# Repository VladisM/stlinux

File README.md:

# STlinux

Simple board with STM32F446 and SDRAM that is capable of running MMU less linux
build. Purpose of this project is to learn new stuffs. It may seems like good
thing to have Linux in such small form factor but it isn't. MMU is somehow
important in security and using this approach to build device that will be
connected to the network is a bad idea.

This project using submodules. After clone use following to init them.

```bash
$ git submodule update --init --recursive
```

## System specification

* Hardware:
    * 32MB SDRAM
    * 8MB QSPI Flash
    * UART console, sd card slot, EEPROM
    * two LEDs and two buttons
* Software
    * Linux kernel 6.3
    * Busybox 1.36.1

## Manufacturing board

Gerber files required for manufacturing are stored in `board/ger` subdirectory.
To manufacture board you shall just find yourself a suitable manufacturer
and use latest archive.

To generate BOM you shall use KiCad and revisit folder `board/kicad`. All
project files are stored there.

After soldering board you should apply ftdi configuration into
integrated UART bridge. Correct configuration is provided
by the file `board/ftdi_configuration.xml`. For that you are going
to need Windows PC and FT_PROG tool (available on their website).

To test if board was correctly manufactured and most importantly
assembled. You can use firmware available in `board_test` folder.

Compile and load firmware, connect using serial port at speed of 115200
and follow instructions.

**Warning:** at this moment SDIO and SD Card slot test are
not implemented!

## Compile system and bootloader

Everything is compiled using clfs.sh script in root folder of this project. So,
if you want to compile whole system simply call following command. (note, adjust
number of cores for compilation using -j)

```bash
$ ./clfs.sh --build all -j 8
```

After some time, you can find all output images in `build/images/`. There are:

 * bootloader - u-boot.bin
 * linux kernel - zImage
 * device tree - stm32f446-stlinux.dtb
 * system image - clfs.uImage

Bootloader shall be loaded to the board using STLink, and shall be written
to the internal Flash memory of MCU.

```bash
st-flash write build/images/u-boot.bin 0x08000000
```

Other components are by default loaded from QSPI Flash, there are two ways how
to get them there.

 * Using SD card
 * Using serial port (legacy)

### Loading QSPI Flash using serial port

This method was used for first revision of board with nonworking SD card slot.
If you have second revision of board, use SD card, it is much more faster.

Once you are in u-boot console, you can use xmodem protocol to send all files
and then write them to the QSPI Flash. For writing there is mtd command. Follow
next code snippet.

```bash
> loadx
# send kernel file (zImage) using your console emulator
> mtd erase kernel
> mtd write kernel ${loadaddr}
> loadx
# send rootfs file (clfs.uImage) using your console emulator
> mtd erase rootfs
> mtd write rootfs ${loadaddr}
> loadx
# send dtb file (stm32f446-stlinux.dtb) using your console emulator
> mtd erase rootfs
> mtd write rootfs ${loadaddr}
```

Then you can simply reset the board or type `run bootcmd` and you should be
welcomed by kernel boot log.

### Loading QSPI Flash using SD card

Compared to using serial port, this one is much much faster because data are
transferred over SD card, not xmodem at 115200 bauds.

Create one partition on your SD card, format it as FAT32, and copy there
image files from build directory. Then insert your card to the board and run
following commands.

```bash
> fatload mmc 0:1 ${loadaddr} zImage
> mtd erase kernel
> mtd write kernel ${loadaddr}
> fatload mmc 0:1 ${loadaddr} clfs.uImage
> mtd erase rootfs
> mtd write rootfs ${loadaddr}
> fatload mmc 0:1 ${loadaddr} stm32f446-stlinux.dtb
> mtd erase dtb
> mtd write dtb ${loadaddr}
```

After reset, your board will boot from QSPI Flash or you can simply type
`run bootcmd`.

### Loading directly from SD card

If you are feeling lazy, just copypaste this to bootloader console. And it will boot.

```bash
fatload mmc 0:1 ${kernel_addr_l} zImage ; fatload mmc 0:1 ${rootfs_addr_l} clfs.uImage ; fatload mmc 0:1 ${dtb_addr_l} stm32f446-stlinux.dtb ; run set_args ; bootz ${kernel_addr_l} ${rootfs_addr_l} ${dtb_addr_l}
```

It will load everything from SD card into RAM and boot kernel that way.

## License

This project is using a lot of software components that are licensed under
various licenses. Always make sure to check what component are you working
with to prevent any misunderstanding.

Board manufacturing files, firmware for testing, and build script is licensed
using the Do What The Fuck You Want To Public License, Version 2,
as published by Sam Hocevar. See COPYING file for more details.

Note: CLFS is abbreviation from Cross Linux From Scratch, in general describing process
of cross compiling [Linux From Scratch](https://www.linuxfromscratch.org/). Please
also see [CLFS project](https://trac.clfs.org/). My work is influenced by these
projects and I learned from their materials a lot.

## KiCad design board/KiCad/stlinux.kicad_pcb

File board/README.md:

# Board project files

In this directory all files required for manufacturing board are gathered.
Archives with gerber files are stored in `CAM` directory. Project for KiCad
can be found in `KiCad` directory. Configuration required for FTDI chip is
next to the gerber files in `CAM` directory. There is also a CubeMX project
located in `STM32CubeMX` folder.

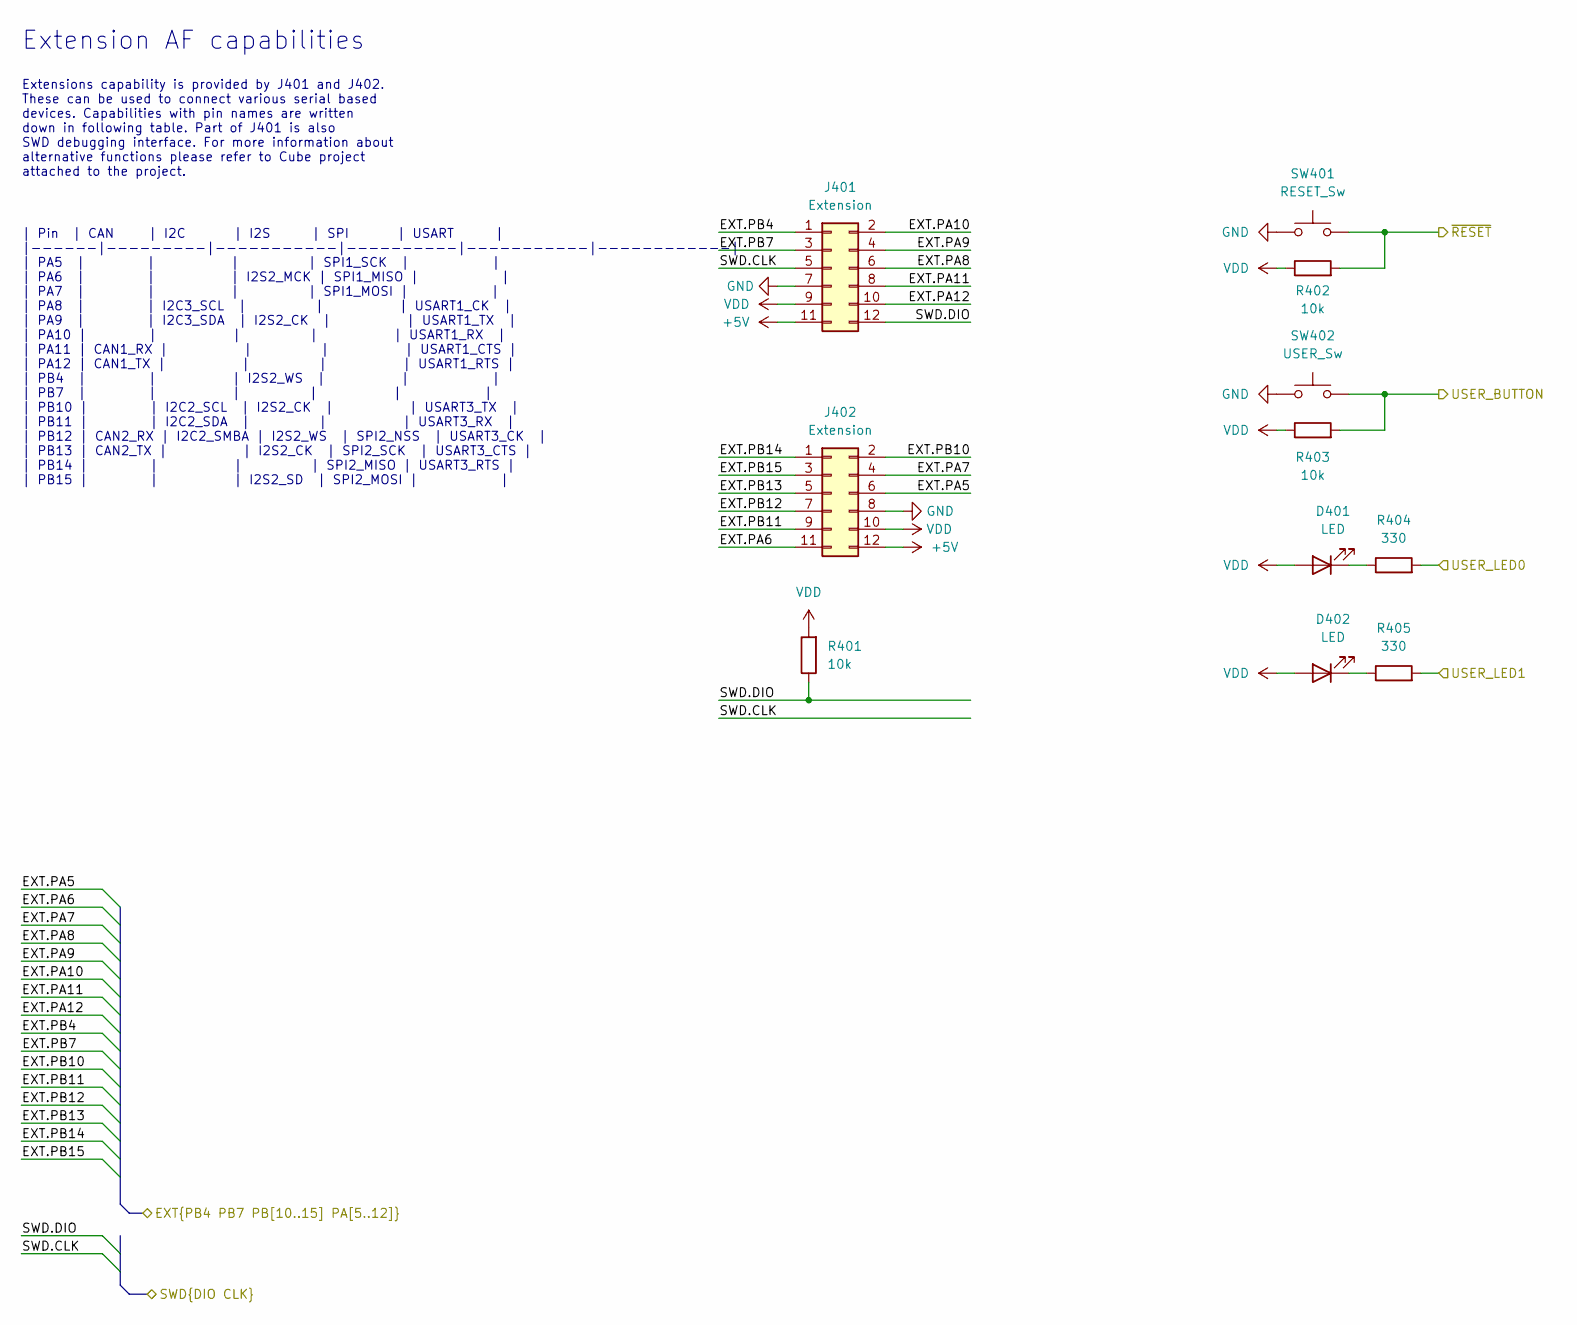
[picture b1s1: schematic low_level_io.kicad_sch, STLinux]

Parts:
D401, D402: LED; LED_1206_3216Metric_Pad1.42x1.75mm_HandSolder
J401, J402: Extension; PinSocket_2x06_P2.54mm_Vertical_SMD
R401, R402, R403: 10k; R_0603_1608Metric_Pad0.98x0.95mm_HandSolder
R404, R405: 330; R_0603_1608Metric_Pad0.98x0.95mm_HandSolder
SW401: RESET_Sw; SW_Push_1P1T_NO_6x6mm_H9.5mm
SW402: USER_Sw; SW_Push_1P1T_NO_6x6mm_H9.5mm

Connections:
+5V: J401.11, J402.12; also elsewhere on the board
/Low level IO/EXT.PA5: J402.6; also elsewhere on the board
/Low level IO/EXT.PA6: J402.11; also elsewhere on the board
/Low level IO/EXT.PA7: J402.4; also elsewhere on the board
/Low level IO/EXT.PA8: J401.6; also elsewhere on the board
/Low level IO/EXT.PA9: J401.4; also elsewhere on the board
/Low level IO/EXT.PA10: J401.2; also elsewhere on the board
/Low level IO/EXT.PA11: J401.8; also elsewhere on the board
/Low level IO/EXT.PA12: J401.10; also elsewhere on the board
/Low level IO/EXT.PB4: J401.1; also elsewhere on the board
/Low level IO/EXT.PB7: J401.3; also elsewhere on the board
/Low level IO/EXT.PB10: J402.2; also elsewhere on the board
/Low level IO/EXT.PB11: J402.9; also elsewhere on the board
/Low level IO/EXT.PB12: J402.7; also elsewhere on the board
/Low level IO/EXT.PB13: J402.5; also elsewhere on the board
/Low level IO/EXT.PB14: J402.1; also elsewhere on the board
/Low level IO/EXT.PB15: J402.3; also elsewhere on the board
/Low level IO/SWD.CLK: J401.5; also elsewhere on the board
/Low level IO/SWD.DIO: J401.12, R401.1; also elsewhere on the board
/Low level IO/USER_BUTTON: R403.2, SW402.2; also elsewhere on the board
/Low level IO/USER_LED0: R404.2; also elsewhere on the board
/Low level IO/USER_LED1: R405.2; also elsewhere on the board
/Low level IO/~RESET: R402.2, SW401.2; also elsewhere on the board
GND: J401.7, J402.8, SW401.1, SW402.1; also elsewhere on the board
unnamed: D401.1 (K), R404.1
unnamed: D402.1 (K), R405.1
VDD: D401.2 (A), D402.2 (A), J401.9, J402.10, R401.2, R402.1, R403.1; also elsewhere on the board

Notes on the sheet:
| Pin | CAN | I2C | I2S | SPI | USART | |------|---------|-----------|----------|-----------|------------| | PA5 | | | | SPI1_SCK | | | PA6 | | | I2S2_MCK | SPI1_MISO | | | PA7 | | | | SPI1_MOSI | | | PA8 | | I2C3_SCL | | | USART1_CK | | PA9 | | I2C3_SDA | I2S2_CK | | USART1_TX | | PA10 | | | | | U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
Extensions capability is provided by J401 and J402. These can be used to connect various serial based devices. Capabilities with pin names are written down in following table. Part of J401 is also SWD debugging interface. For more information about alternative functions please refer to Cube project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
Extension AF capabilities

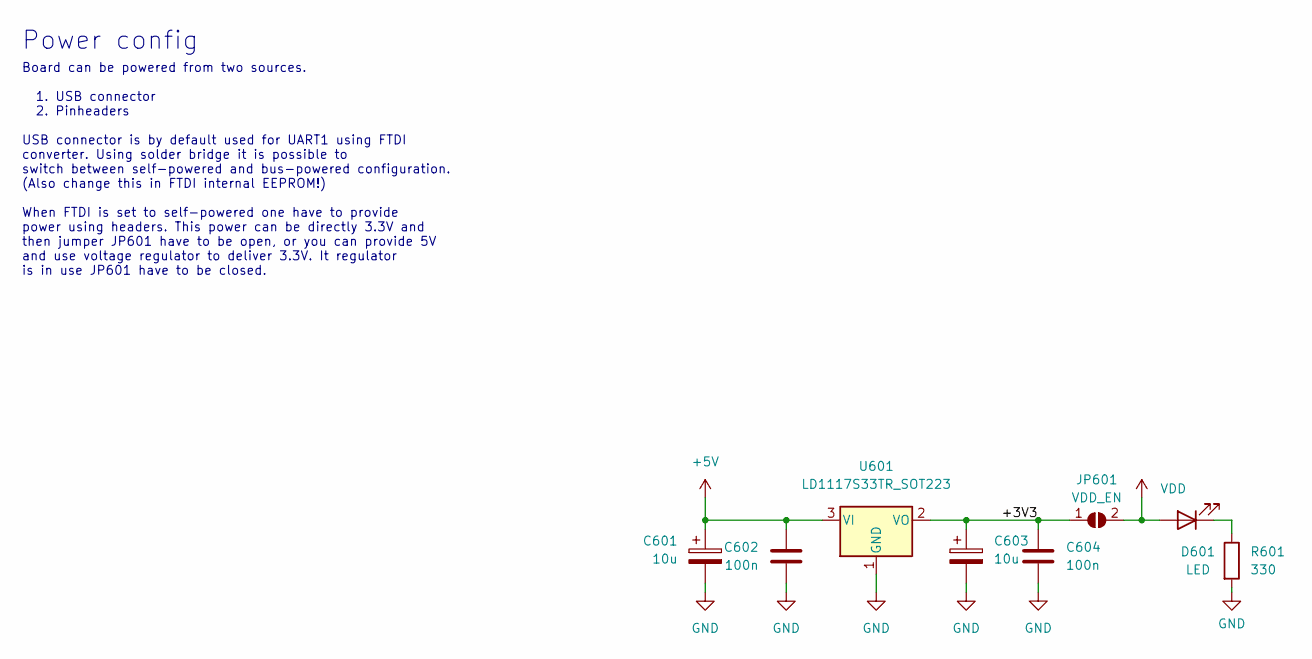
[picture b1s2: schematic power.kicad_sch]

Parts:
C601, C603: 10u; CP_EIA-3216-18_Kemet-A_Pad1.58x1.35mm_HandSolder
C602, C604: 100n; C_0603_1608Metric_Pad1.08x0.95mm_HandSolder
D601: LED; LED_1206_3216Metric_Pad1.42x1.75mm_HandSolder
JP601: VDD_EN; SolderJumper-2_P1.3mm_Open_RoundedPad1.0x1.5mm
R601: 330; R_0603_1608Metric_Pad0.98x0.95mm_HandSolder
U601: LD1117S33TR_SOT223; SOT-223-3_TabPin2

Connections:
+5V: C601.1, C602.1, U601.3 (VI); also elsewhere on the board
/Power/+3V3: C603.1, C604.1, JP601.1 (A), U601.2 (VO)
GND: C601.2, C602.2, C603.2, C604.2, R601.2, U601.1 (GND); also elsewhere on the board
unnamed: D601.1 (K), R601.1
VDD: D601.2 (A), JP601.2 (B); also elsewhere on the board

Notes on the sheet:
Power config
Board can be powered from two sources. 1. USB connector 2. Pinheaders USB connector is by default used for UART1 using FTDI converter. Using solder bridge it is possible to switch between self-powered and bus-powered configuration. (Also change this in FTDI internal EEPROM!) When FTDI is set to sel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

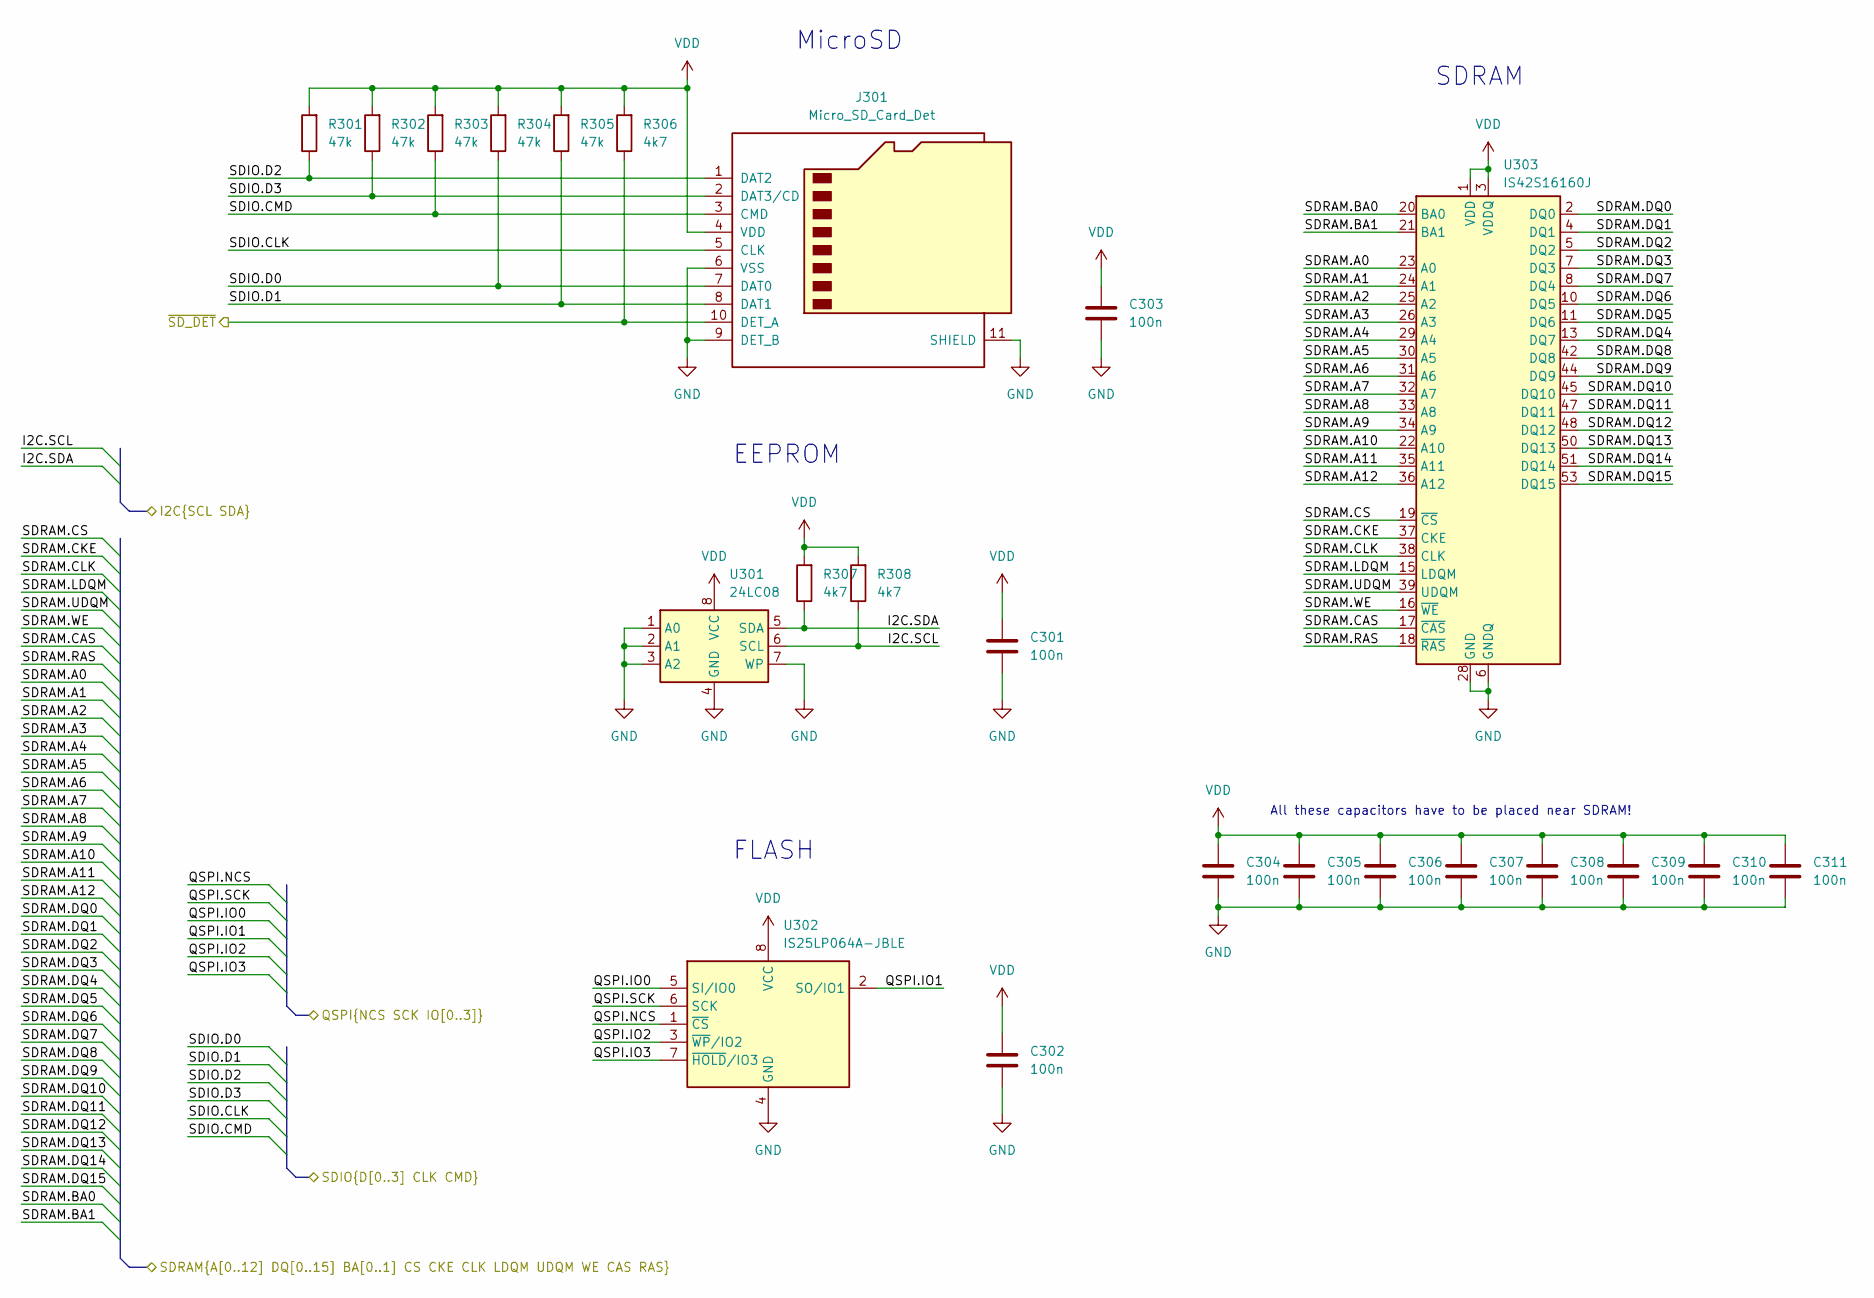
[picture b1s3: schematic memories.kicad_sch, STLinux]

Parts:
C301, C302, C303, C304, C305, C306, C307, C308, C309, C310, C311: 100n; C_0603_1608Metric_Pad1.08x0.95mm_HandSolder
J301: Micro_SD_Card_Det; microSD_HC_Molex_104031-0811
R301, R302, R303, R304, R305: 47k; R_0603_1608Metric_Pad0.98x0.95mm_HandSolder
R306, R307, R308: 4k7; R_0603_1608Metric_Pad0.98x0.95mm_HandSolder
U301: 24LC08; SOP-8_3.9x4.9mm_P1.27mm
U302: IS25LP064A-JBLE; SOIC-8_5.23x5.23mm_P1.27mm
U303: IS42S16160J; TSOP-II-54_22.2x10.16mm_P0.8mm

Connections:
/MCU/I2C.SCL: R308.1, U301.6 (SCL); also elsewhere on the board
/MCU/I2C.SDA: R307.1, U301.5 (SDA); also elsewhere on the board
/MCU/QSPI.IO0: U302.5 (SI/IO0); also elsewhere on the board
/MCU/QSPI.IO1: U302.2 (SO/IO1); also elsewhere on the board
/MCU/QSPI.IO2: U302.3 (~WP/IO2); also elsewhere on the board
/MCU/QSPI.IO3: U302.7 (~HOLD/IO3); also elsewhere on the board
/MCU/QSPI.NCS: U302.1 (~CS); also elsewhere on the board
/MCU/QSPI.SCK: U302.6 (SCK); also elsewhere on the board
/MCU/SDIO.CLK: J301.5 (CLK); also elsewhere on the board
/MCU/SDIO.CMD: J301.3 (CMD), R303.1; also elsewhere on the board
/MCU/SDIO.D0: J301.7 (DAT0), R304.1; also elsewhere on the board
/MCU/SDIO.D1: J301.8 (DAT1), R305.1; also elsewhere on the board
/MCU/SDIO.D2: J301.1 (DAT2), R301.1; also elsewhere on the board
/MCU/SDIO.D3: J301.2 (DAT3/CD), R302.1; also elsewhere on the board
/MCU/SDRAM.A0: U303.23 (A0); also elsewhere on the board
/MCU/SDRAM.A1: U303.24 (A1); also elsewhere on the board
/MCU/SDRAM.A2: U303.25 (A2); also elsewhere on the board
/MCU/SDRAM.A3: U303.26 (A3); also elsewhere on the board
/MCU/SDRAM.A4: U303.29 (A4); also elsewhere on the board
/MCU/SDRAM.A5: U303.30 (A5); also elsewhere on the board
/MCU/SDRAM.A6: U303.31 (A6); also elsewhere on the board
/MCU/SDRAM.A7: U303.32 (A7); also elsewhere on the board
/MCU/SDRAM.A8: U303.33 (A8); also elsewhere on the board
/MCU/SDRAM.A9: U303.34 (A9); also elsewhere on the board
/MCU/SDRAM.A10: U303.22 (A10); also elsewhere on the board
/MCU/SDRAM.A11: U303.35 (A11); also elsewhere on the board
/MCU/SDRAM.A12: U303.36 (A12); also elsewhere on the board
/MCU/SDRAM.BA0: U303.20 (BA0); also elsewhere on the board
/MCU/SDRAM.BA1: U303.21 (BA1); also elsewhere on the board
/MCU/SDRAM.CAS: U303.17 (~CAS); also elsewhere on the board
/MCU/SDRAM.CKE: U303.37 (CKE); also elsewhere on the board
/MCU/SDRAM.CLK: U303.38 (CLK); also elsewhere on the board
/MCU/SDRAM.CS: U303.19 (~CS); also elsewhere on the board
/MCU/SDRAM.DQ0: U303.2 (DQ0); also elsewhere on the board
/MCU/SDRAM.DQ1: U303.4 (DQ1); also elsewhere on the board
/MCU/SDRAM.DQ2: U303.5 (DQ2); also elsewhere on the board
/MCU/SDRAM.DQ3: U303.7 (DQ3); also elsewhere on the board
/MCU/SDRAM.DQ4: U303.13 (DQ7); also elsewhere on the board
/MCU/SDRAM.DQ5: U303.11 (DQ6); also elsewhere on the board
/MCU/SDRAM.DQ6: U303.10 (DQ5); also elsewhere on the board
/MCU/SDRAM.DQ7: U303.8 (DQ4); also elsewhere on the board
/MCU/SDRAM.DQ8: U303.42 (DQ8); also elsewhere on the board
/MCU/SDRAM.DQ9: U303.44 (DQ9); also elsewhere on the board
/MCU/SDRAM.DQ10: U303.45 (DQ10); also elsewhere on the board
/MCU/SDRAM.DQ11: U303.47 (DQ11); also elsewhere on the board
/MCU/SDRAM.DQ12: U303.48 (DQ12); also elsewhere on the board
/MCU/SDRAM.DQ13: U303.50 (DQ13); also elsewhere on the board
/MCU/SDRAM.DQ14: U303.51 (DQ14); also elsewhere on the board
/MCU/SDRAM.DQ15: U303.53 (DQ15); also elsewhere on the board
/MCU/SDRAM.LDQM: U303.15 (LDQM); also elsewhere on the board
/MCU/SDRAM.RAS: U303.18 (~RAS); also elsewhere on the board
/MCU/SDRAM.UDQM: U303.39 (UDQM); also elsewhere on the board
/MCU/SDRAM.WE: U303.16 (~WE); also elsewhere on the board
/MCU/~SD_DET: J301.10 (DET_A), R306.1; also elsewhere on the board
GND: C301.2, C302.2, C303.2, C304.2, C305.2, C306.2, C307.2, C308.2, C309.2, C310.2, C311.2, J301.6 (VSS), J301.9 (DET_B), J301.11 (SHIELD), U301.1 (A0), U301.2 (A1), U301.3 (A2), U301.4 (GND), U301.7 (WP), U302.4 (GND), U303.6 (GNDQ), U303.12 (GNDQ), U303.28 (GND), U303.41 (GND), U303.46 (GNDQ), U303.52 (GNDQ), U303.54 (GND); also elsewhere on the board
VDD: C301.1, C302.1, C303.1, C304.1, C305.1, C306.1, C307.1, C308.1, C309.1, C310.1, C311.1, J301.4 (VDD), R301.2, R302.2, R303.2, R304.2, R305.2, R306.2, R307.2, R308.2, U301.8 (VCC), U302.8 (VCC), U303.1 (VDD), U303.3 (VDDQ), U303.9 (VDDQ), U303.14 (VDD), U303.27 (VDD), U303.43 (VDDQ), U303.49 (VDDQ); also elsewhere on the board

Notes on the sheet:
EEPROM
All these capacitors have to be placed near SDRAM!
FLASH
MicroSD
SDRAM

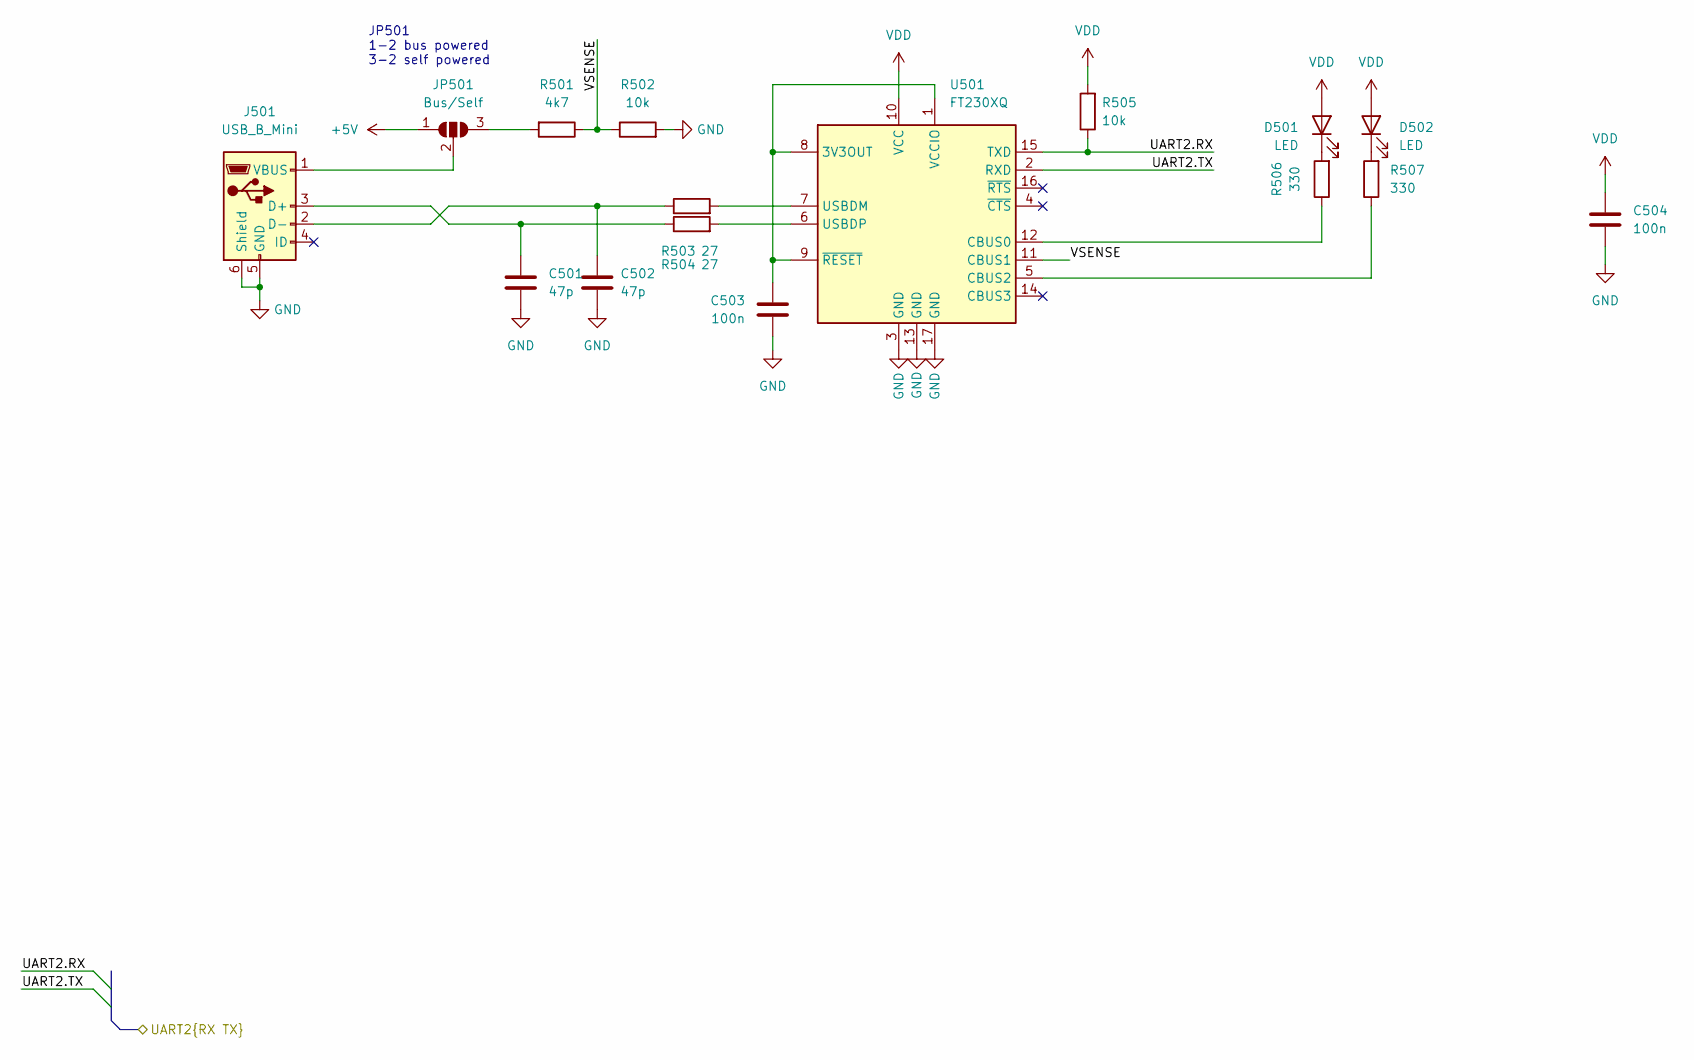
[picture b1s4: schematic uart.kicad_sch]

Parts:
C501, C502: 47p; C_0603_1608Metric_Pad1.08x0.95mm_HandSolder
C503, C504: 100n; C_0603_1608Metric_Pad1.08x0.95mm_HandSolder
D501, D502: LED; LED_1206_3216Metric_Pad1.42x1.75mm_HandSolder
J501: USB_B_Mini; USB_Mini-B_Wuerth_65100516121_Horizontal
JP501: Bus/Self; SolderJumper-3_P1.3mm_Open_RoundedPad1.0x1.5mm_NumberLabels
R501: 4k7; R_0603_1608Metric_Pad0.98x0.95mm_HandSolder
R502, R505: 10k; R_0603_1608Metric_Pad0.98x0.95mm_HandSolder
R503, R504: 27; R_0603_1608Metric_Pad0.98x0.95mm_HandSolder
R506, R507: 330; R_0603_1608Metric_Pad0.98x0.95mm_HandSolder
U501: FT230XQ; QFN-16-1EP_4x4mm_P0.65mm_EP2.1x2.1mm

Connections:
+5V: JP501.1 (A); also elsewhere on the board
/MCU/UART2.RX: R505.1, U501.15 (TXD); also elsewhere on the board
/MCU/UART2.TX: U501.2 (RXD); also elsewhere on the board
/UART/VSENSE: R501.1, R502.1, U501.11 (CBUS1)
GND: C501.2, C502.2, C503.2, C504.2, J501.5 (GND), J501.6 (Shield), R502.2, U501.3 (GND), U501.13 (GND), U501.17 (GND); also elsewhere on the board
unnamed: D501.1 (K), R506.2
unnamed: D502.1 (K), R507.2
unnamed: C501.1, J501.3 (D+), R504.1
unnamed: C502.1, J501.2 (D-), R503.1
unnamed: J501.1 (VBUS), JP501.2 (C)
unnamed: JP501.3 (B), R501.2
unnamed: C503.1, U501.1 (VCCIO), U501.8 (3V3OUT), U501.9 (~RESET)
unnamed: R506.1, U501.12 (CBUS0)
unnamed: R507.1, U501.5 (CBUS2)
unnamed: R503.2, U501.7 (USBDM)
unnamed: R504.2, U501.6 (USBDP)
VDD: C504.1, D501.2 (A), D502.2 (A), R505.2, U501.10 (VCC); also elsewhere on the board

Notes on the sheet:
JP501 1-2 bus powered 3-2 self powered

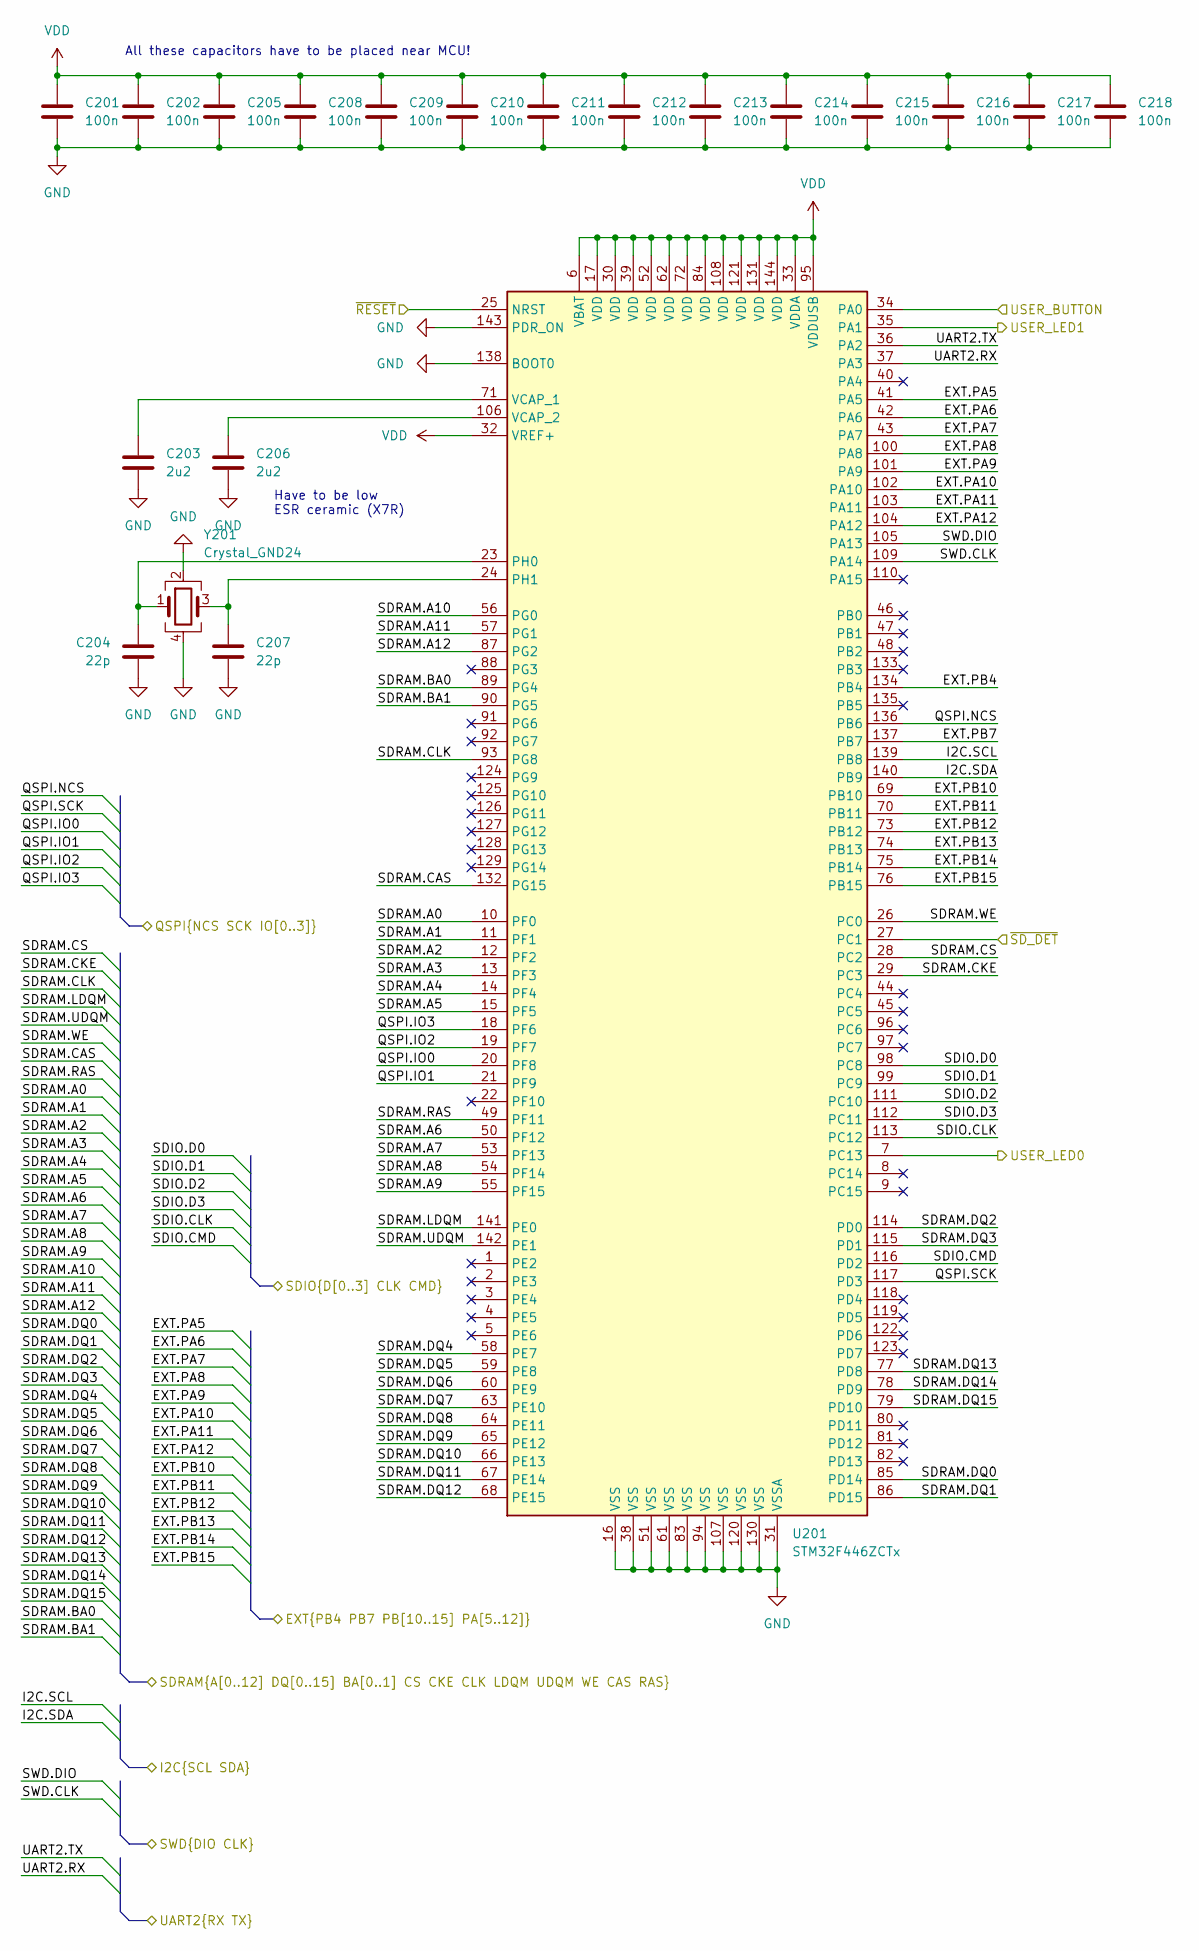
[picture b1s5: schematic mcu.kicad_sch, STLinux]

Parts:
C201, C202, C205, C208, C209, C210, C211, C212, C213, C214, C215, C216, C217, C218: 100n; C_0603_1608Metric_Pad1.08x0.95mm_HandSolder
C203, C206: 2u2; C_0603_1608Metric_Pad1.08x0.95mm_HandSolder
C204, C207: 22p; C_0603_1608Metric_Pad1.08x0.95mm_HandSolder
U201: STM32F446ZCTx; LQFP-144_20x20mm_P0.5mm
Y201: Crystal_GND24; Crystal_SMD_3225-4Pin_3.2x2.5mm_HandSoldering

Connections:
/Low level IO/EXT.PA5: U201.41 (PA5); also elsewhere on the board
/Low level IO/EXT.PA6: U201.42 (PA6); also elsewhere on the board
/Low level IO/EXT.PA7: U201.43 (PA7); also elsewhere on the board
/Low level IO/EXT.PA8: U201.100 (PA8); also elsewhere on the board
/Low level IO/EXT.PA9: U201.101 (PA9); also elsewhere on the board
/Low level IO/EXT.PA10: U201.102 (PA10); also elsewhere on the board
/Low level IO/EXT.PA11: U201.103 (PA11); also elsewhere on the board
/Low level IO/EXT.PA12: U201.104 (PA12); also elsewhere on the board
/Low level IO/EXT.PB4: U201.134 (PB4); also elsewhere on the board
/Low level IO/EXT.PB7: U201.137 (PB7); also elsewhere on the board
/Low level IO/EXT.PB10: U201.69 (PB10); also elsewhere on the board
/Low level IO/EXT.PB11: U201.70 (PB11); also elsewhere on the board
/Low level IO/EXT.PB12: U201.73 (PB12); also elsewhere on the board
/Low level IO/EXT.PB13: U201.74 (PB13); also elsewhere on the board
/Low level IO/EXT.PB14: U201.75 (PB14); also elsewhere on the board
/Low level IO/EXT.PB15: U201.76 (PB15); also elsewhere on the board
/Low level IO/SWD.CLK: U201.109 (PA14); also elsewhere on the board
/Low level IO/SWD.DIO: U201.105 (PA13); also elsewhere on the board
/Low level IO/USER_BUTTON: U201.34 (PA0); also elsewhere on the board
/Low level IO/USER_LED0: U201.7 (PC13); also elsewhere on the board
/Low level IO/USER_LED1: U201.35 (PA1); also elsewhere on the board
/Low level IO/~RESET: U201.25 (NRST); also elsewhere on the board
/MCU/I2C.SCL: U201.139 (PB8); also elsewhere on the board
/MCU/I2C.SDA: U201.140 (PB9); also elsewhere on the board
/MCU/QSPI.IO0: U201.20 (PF8); also elsewhere on the board
/MCU/QSPI.IO1: U201.21 (PF9); also elsewhere on the board
/MCU/QSPI.IO2: U201.19 (PF7); also elsewhere on the board
/MCU/QSPI.IO3: U201.18 (PF6); also elsewhere on the board
/MCU/QSPI.NCS: U201.136 (PB6); also elsewhere on the board
/MCU/QSPI.SCK: U201.117 (PD3); also elsewhere on the board
/MCU/SDIO.CLK: U201.113 (PC12); also elsewhere on the board
/MCU/SDIO.CMD: U201.116 (PD2); also elsewhere on the board
/MCU/SDIO.D0: U201.98 (PC8); also elsewhere on the board
/MCU/SDIO.D1: U201.99 (PC9); also elsewhere on the board
/MCU/SDIO.D2: U201.111 (PC10); also elsewhere on the board
/MCU/SDIO.D3: U201.112 (PC11); also elsewhere on the board
/MCU/SDRAM.A0: U201.10 (PF0); also elsewhere on the board
/MCU/SDRAM.A1: U201.11 (PF1); also elsewhere on the board
/MCU/SDRAM.A2: U201.12 (PF2); also elsewhere on the board
/MCU/SDRAM.A3: U201.13 (PF3); also elsewhere on the board
/MCU/SDRAM.A4: U201.14 (PF4); also elsewhere on the board
/MCU/SDRAM.A5: U201.15 (PF5); also elsewhere on the board
/MCU/SDRAM.A6: U201.50 (PF12); also elsewhere on the board
/MCU/SDRAM.A7: U201.53 (PF13); also elsewhere on the board
/MCU/SDRAM.A8: U201.54 (PF14); also elsewhere on the board
/MCU/SDRAM.A9: U201.55 (PF15); also elsewhere on the board
/MCU/SDRAM.A10: U201.56 (PG0); also elsewhere on the board
/MCU/SDRAM.A11: U201.57 (PG1); also elsewhere on the board
/MCU/SDRAM.A12: U201.87 (PG2); also elsewhere on the board
/MCU/SDRAM.BA0: U201.89 (PG4); also elsewhere on the board
/MCU/SDRAM.BA1: U201.90 (PG5); also elsewhere on the board
/MCU/SDRAM.CAS: U201.132 (PG15); also elsewhere on the board
/MCU/SDRAM.CKE: U201.29 (PC3); also elsewhere on the board
/MCU/SDRAM.CLK: U201.93 (PG8); also elsewhere on the board
/MCU/SDRAM.CS: U201.28 (PC2); also elsewhere on the board
/MCU/SDRAM.DQ0: U201.85 (PD14); also elsewhere on the board
/MCU/SDRAM.DQ1: U201.86 (PD15); also elsewhere on the board
/MCU/SDRAM.DQ2: U201.114 (PD0); also elsewhere on the board
/MCU/SDRAM.DQ3: U201.115 (PD1); also elsewhere on the board
/MCU/SDRAM.DQ4: U201.58 (PE7); also elsewhere on the board
/MCU/SDRAM.DQ5: U201.59 (PE8); also elsewhere on the board
/MCU/SDRAM.DQ6: U201.60 (PE9); also elsewhere on the board
/MCU/SDRAM.DQ7: U201.63 (PE10); also elsewhere on the board
/MCU/SDRAM.DQ8: U201.64 (PE11); also elsewhere on the board
/MCU/SDRAM.DQ9: U201.65 (PE12); also elsewhere on the board
/MCU/SDRAM.DQ10: U201.66 (PE13); also elsewhere on the board
/MCU/SDRAM.DQ11: U201.67 (PE14); also elsewhere on the board
/MCU/SDRAM.DQ12: U201.68 (PE15); also elsewhere on the board
/MCU/SDRAM.DQ13: U201.77 (PD8); also elsewhere on the board
/MCU/SDRAM.DQ14: U201.78 (PD9); also elsewhere on the board
/MCU/SDRAM.DQ15: U201.79 (PD10); also elsewhere on the board
/MCU/SDRAM.LDQM: U201.141 (PE0); also elsewhere on the board
/MCU/SDRAM.RAS: U201.49 (PF11); also elsewhere on the board
/MCU/SDRAM.UDQM: U201.142 (PE1); also elsewhere on the board
/MCU/SDRAM.WE: U201.26 (PC0); also elsewhere on the board
/MCU/UART2.RX: U201.37 (PA3); also elsewhere on the board
/MCU/UART2.TX: U201.36 (PA2); also elsewhere on the board
/MCU/~SD_DET: U201.27 (PC1); also elsewhere on the board
GND: C201.2, C202.2, C203.2, C204.2, C205.2, C206.2, C207.2, C208.2, C209.2, C210.2, C211.2, C212.2, C213.2, C214.2, C215.2, C216.2, C217.2, C218.2, U201.16 (VSS), U201.31 (VSSA), U201.38 (VSS), U201.51 (VSS), U201.61 (VSS), U201.83 (VSS), U201.94 (VSS), U201.107 (VSS), U201.120 (VSS), U201.130 (VSS), U201.138 (BOOT0), U201.143 (PDR_ON), Y201.2, Y201.4; also elsewhere on the board
unnamed: C204.1, U201.23 (PH0), Y201.1
unnamed: C207.1, U201.24 (PH1), Y201.3
unnamed: C203.1, U201.71 (VCAP_1)
unnamed: C206.1, U201.106 (VCAP_2)
VDD: C201.1, C202.1, C205.1, C208.1, C209.1, C210.1, C211.1, C212.1, C213.1, C214.1, C215.1, C216.1, C217.1, C218.1, U201.6 (VBAT), U201.17 (VDD), U201.30 (VDD), U201.32 (VREF+), U201.33 (VDDA), U201.39 (VDD), U201.52 (VDD), U201.62 (VDD), U201.72 (VDD), U201.84 (VDD), U201.95 (VDDUSB), U201.108 (VDD), U201.121 (VDD), U201.131 (VDD), U201.144 (VDD); also elsewhere on the board

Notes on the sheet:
Have to be low ESR ceramic (X7R)
All these capacitors have to be placed near MCU!

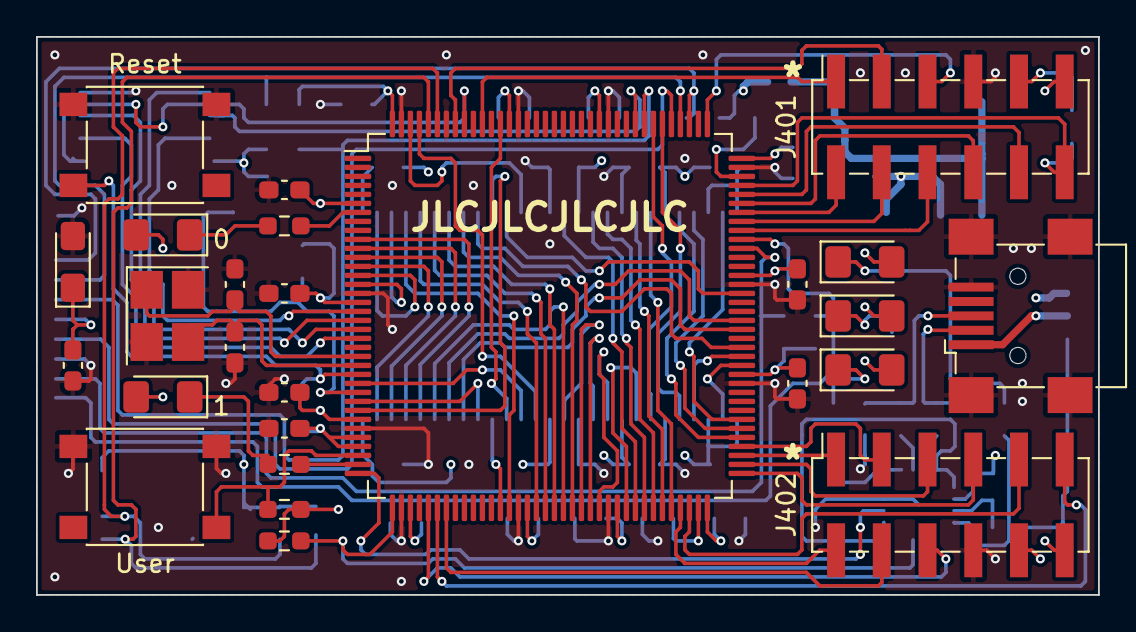
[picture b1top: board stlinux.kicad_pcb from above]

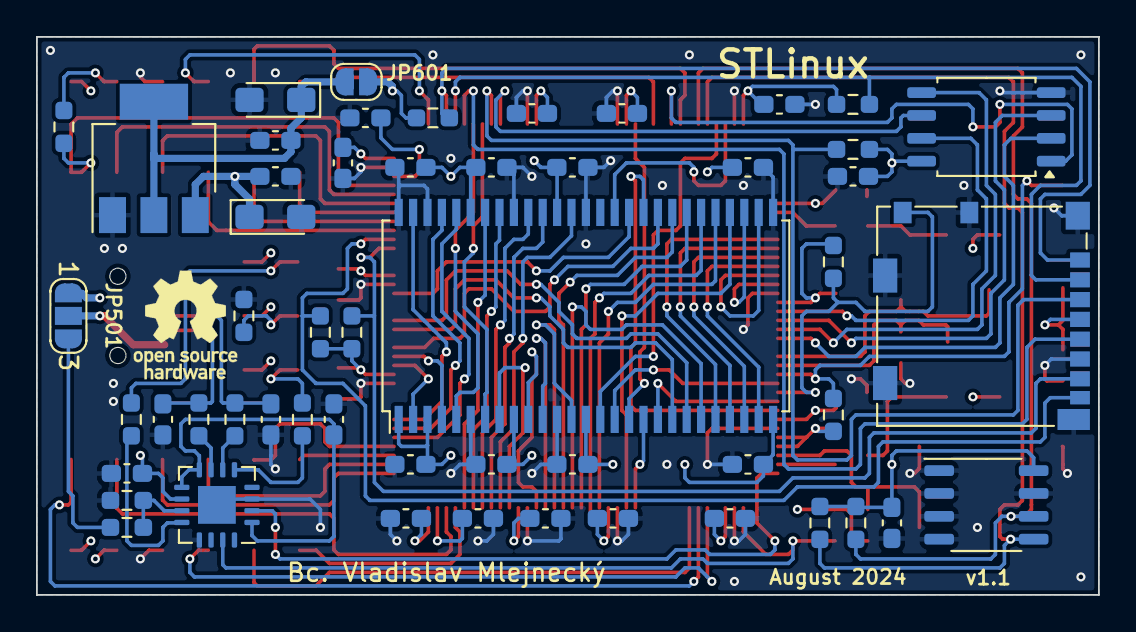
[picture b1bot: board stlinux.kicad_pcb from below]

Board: 4 copper layers, 59.0 x 31.0 mm, 79 parts (53 on the bottom side), 101 nets.

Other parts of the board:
C304#2: 100n; C_0603_1608Metric_Pad1.08x0.95mm_HandSolder

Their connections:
GND: C304#2.2; also elsewhere on the board
VDD: C304#2.1; also elsewhere on the board

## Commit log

2023-03-11 Add schematic, documentation and STM32CubeMX configuration
2023-03-11 Add configuration for onboard FTDI chip
2023-03-11 Added OSHW logo on the board
2023-03-11 Add readme and license
2023-03-11 Added more expansion capability.
2023-03-11 Add JLCPCB order ID placeholder under IC
2023-03-11 Add gerber from first prototypes
2023-03-11 Replaced FTDI package with QFN one
2023-04-18 Add script for obtaining toolchain
2023-05-06 Added mcu_libs as submodule
2023-05-06 Add board test code
2023-05-07 Added additional apnote about migrating F429 to F446
2023-06-25 Gathered board files to one place
2023-06-25 Readme update
2023-07-23 Added submodules for all system parts
2023-09-10 Updated submodules with u-boot and linux port
2023-09-10 Add basic CLFS-like system
2023-09-10 Updated readme and gitignore
2023-09-29 fix build script
2024-08-10 Update board to revision 1.1
    HW bugs fixed:
    * SDIO bus missing pull-up resistors
    * USB bus to FTDI connected wrongly
    * Wrong package of QSPI Flash
    Additionally:
    * Updated version of CubeMX project
2024-08-11 Provided SD card support
2024-08-13 Improve information about booting
2024-08-15 Now using submodules any more for system
2024-08-16 Small fixes
2024-08-16 Fix menuconfig issues with ncurses
2024-08-17 Small fix
2024-08-17 Provide kernel support for filesystems
2024-09-28 Upgrade kernel version to 6.11 and fix problems with EXTI
